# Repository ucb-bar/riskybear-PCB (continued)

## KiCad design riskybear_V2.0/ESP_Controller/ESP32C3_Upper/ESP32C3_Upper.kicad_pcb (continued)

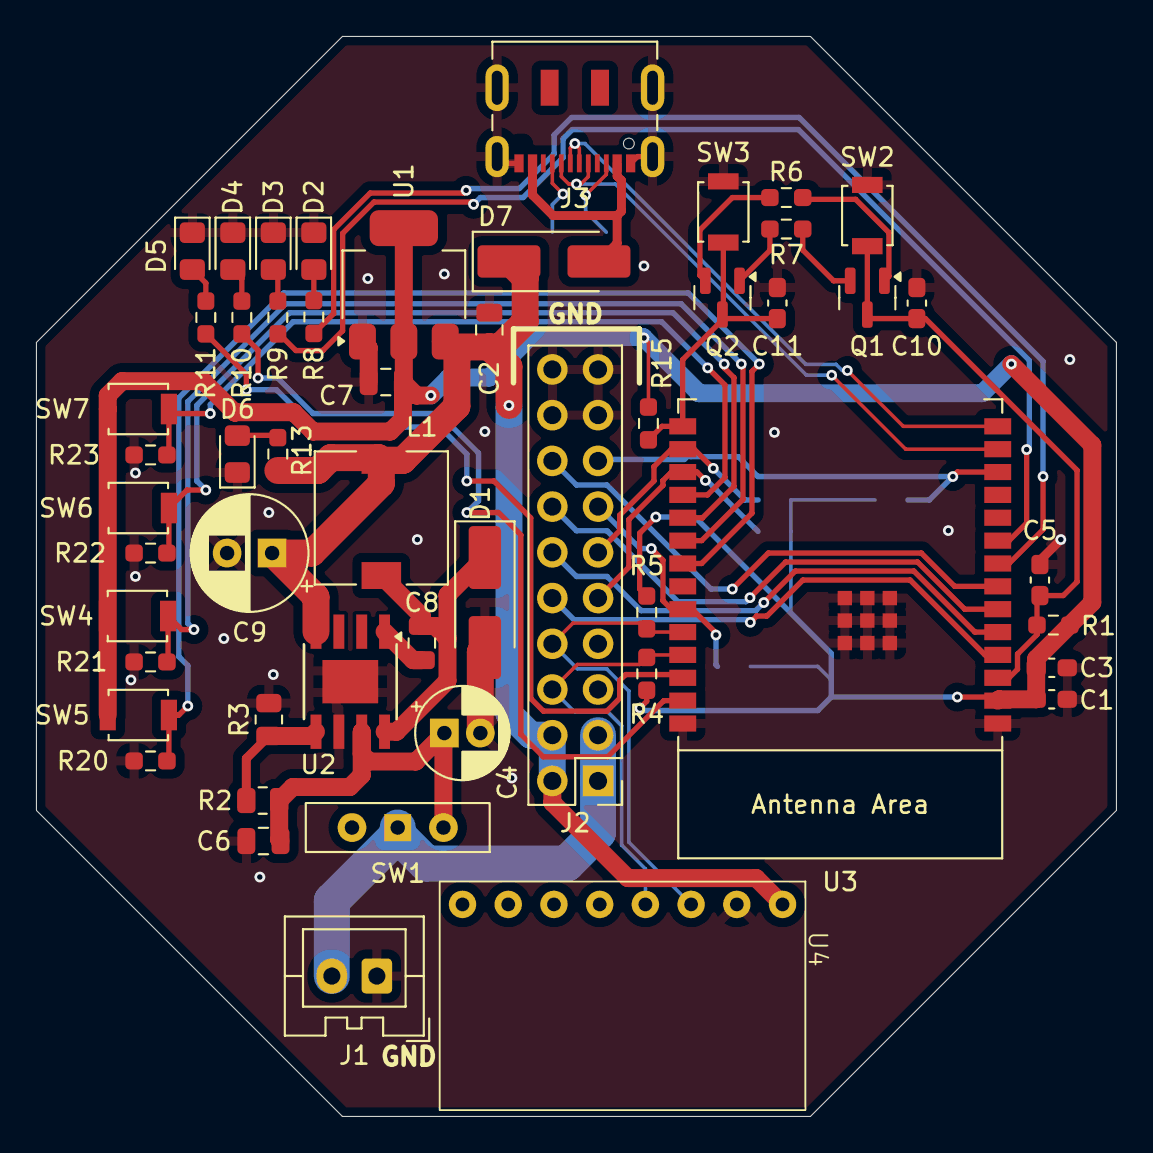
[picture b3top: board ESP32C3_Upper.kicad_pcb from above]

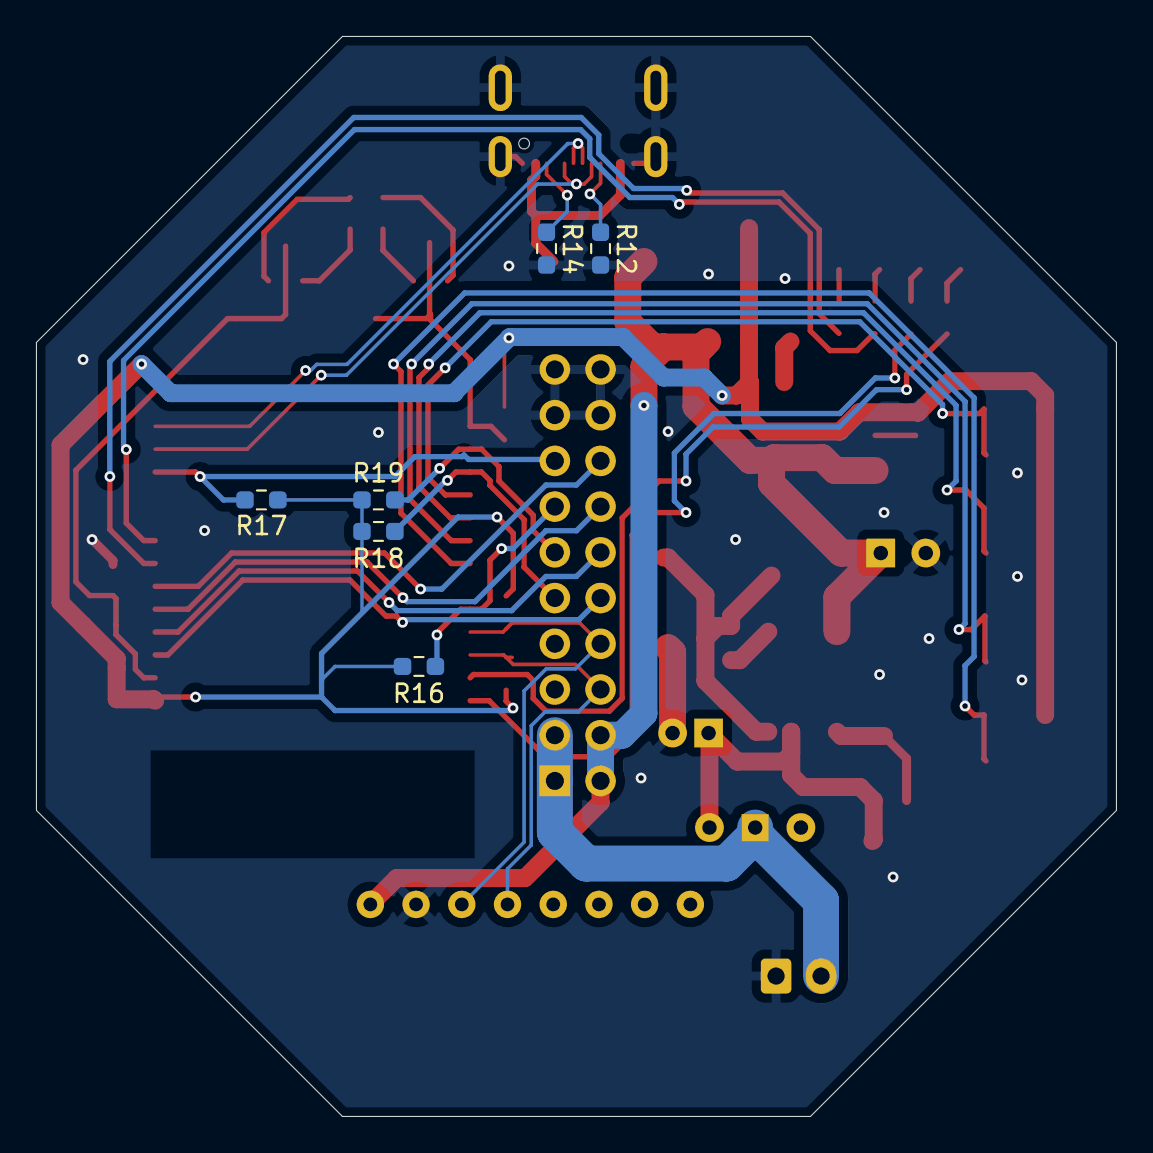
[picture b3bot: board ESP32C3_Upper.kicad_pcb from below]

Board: 2 copper layers, 60.0 x 60.0 mm, 58 parts (6 on the bottom side), 42 nets.

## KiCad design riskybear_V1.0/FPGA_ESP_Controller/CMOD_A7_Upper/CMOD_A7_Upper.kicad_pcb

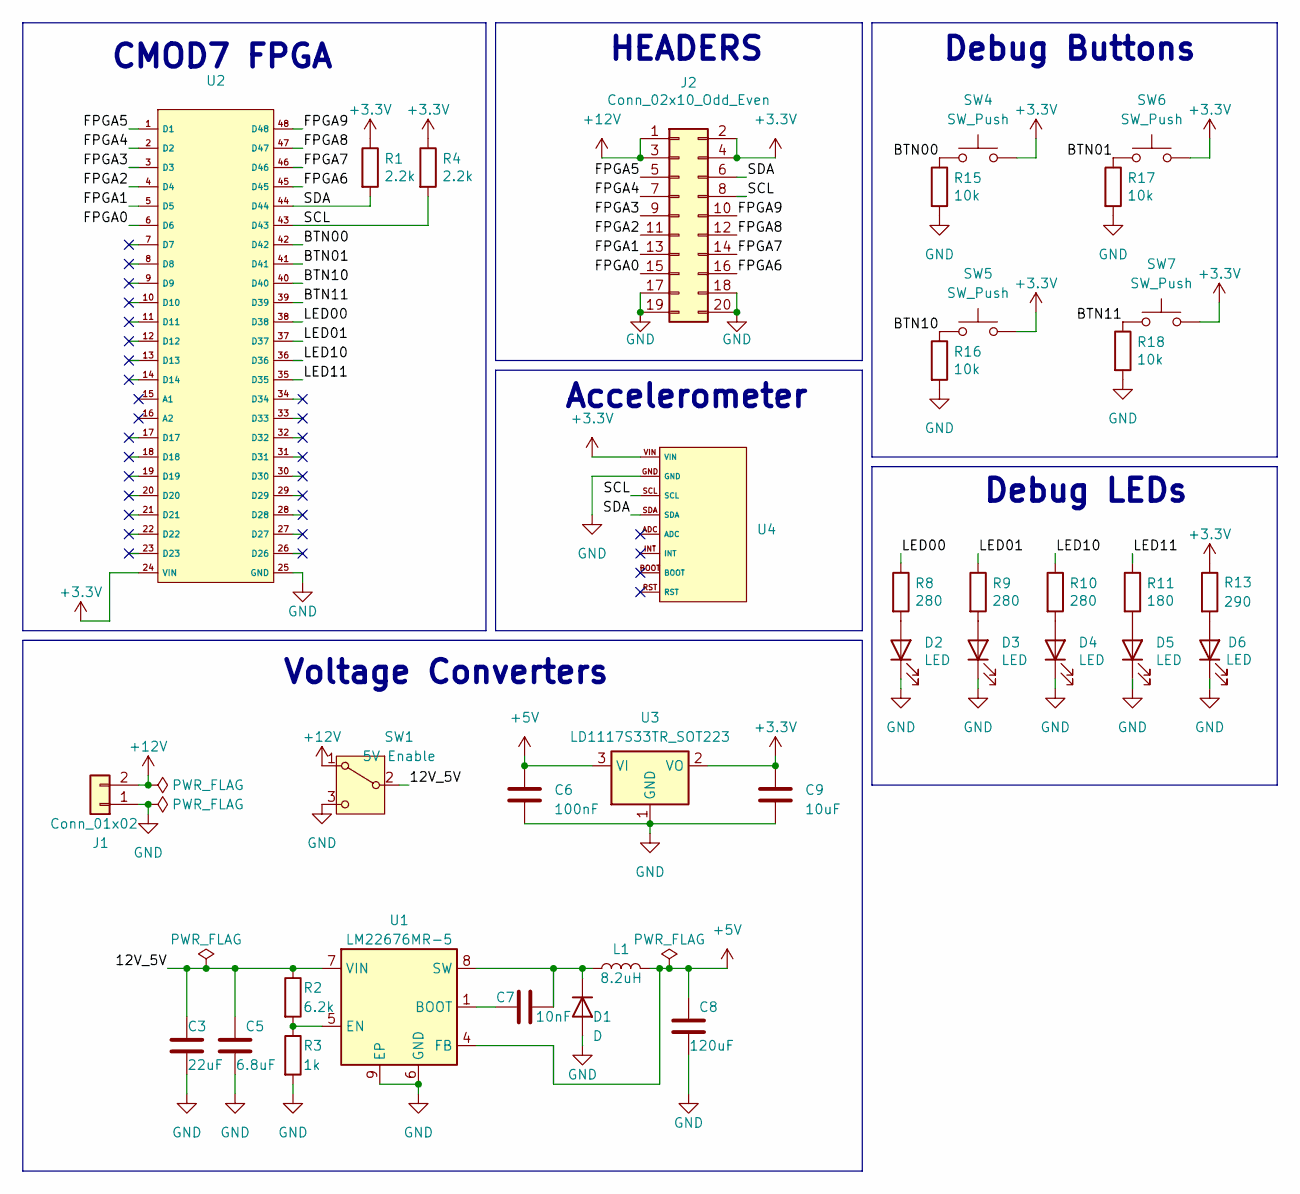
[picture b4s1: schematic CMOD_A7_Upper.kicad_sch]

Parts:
C3: 22uF; CP_Radial_D5.0mm_P2.00mm
C5: 6.8uF; C_0805_2012Metric
C6: 100nF; C_0805_2012Metric
C7: 10nF; C_0805_2012Metric
C8: 120uF; CP_Radial_D6.3mm_P2.50mm
C9: 10uF; C_0805_2012Metric
D1: D; D_SMA_Handsoldering
D2, D3, D4, D5, D6: LED; LED_0805_2012Metric_Pad1.15x1.40mm_HandSolder
J1: Conn_01x02; JST_XA_B02B-XASK-1_1x02_P2.50mm_Vertical
J2: Conn_02x10_Odd_Even; PinHeader_2x10_P2.54mm_Vertical
L1: 8.2uH; L_7.3x7.3_H3.5
R1, R4: 2.2k; R_0603_1608Metric_Pad0.98x0.95mm_HandSolder
R2: 6.2k; R_0805_2012Metric
R3: 1k; R_0805_2012Metric
R8, R9, R10: 280; R_0603_1608Metric_Pad0.98x0.95mm_HandSolder
R11: 180; R_0603_1608Metric_Pad0.98x0.95mm_HandSolder
R13: 290; R_0603_1608Metric_Pad0.98x0.95mm_HandSolder
R15, R16, R17, R18: 10k; R_0603_1608Metric_Pad0.98x0.95mm_HandSolder
SW1: 5V Enable; SW_Slide-03_Wuerth-WS-SLTV_10x2.5x6.4_P2.54mm
SW4, SW5, SW6, SW7: SW_Push; SW_SPST_B3U-1000P
U1: LM22676MR-5; TI_SO-PowerPAD-8
U2: CMODA7
U3: LD1117S33TR_SOT223; SOT-223-3_TabPin2
U4: BNO055

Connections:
+3.3V: C9.1, J2.2, J2.4, R1.1, R4.1, R13.1, SW4.2, SW5.2, SW6.2, SW7.2, U2.24 (VIN), U3.2 (VO), U4.VIN
+5V: C6.1, C8.1, L1.2, U1.4 (FB), U3.3 (VI)
+12V: J1.2, J2.1, J2.3, SW1.1 (A)
/12V_5V: C3.1, C5.1, R2.1, SW1.2 (B), U1.7 (VIN)
/BTN00: R15.1, SW4.1, U2.42 (D42)
/BTN01: R17.1, SW6.1, U2.41 (D41)
/BTN10: R16.1, SW5.1, U2.40 (D40)
/BTN11: R18.1, SW7.1, U2.39 (D39)
/FPGA0: J2.15, U2.6 (D6)
/FPGA1: J2.13, U2.5 (D5)
/FPGA2: J2.11, U2.4 (D4)
/FPGA3: J2.9, U2.3 (D3)
/FPGA4: J2.7, U2.2 (D2)
/FPGA5: J2.5, U2.1 (D1)
/FPGA6: J2.16, U2.45 (D45)
/FPGA7: J2.14, U2.46 (D46)
/FPGA8: J2.12, U2.47 (D47)
/FPGA9: J2.10, U2.48 (D48)
/LED00: R8.1, U2.38 (D38)
/LED01: R9.1, U2.37 (D37)
/LED10: R10.1, U2.36 (D36)
/LED11: R11.1, U2.35 (D35)
/SCL: J2.8, R4.2, U2.43 (D43), U4.SCL
/SDA: J2.6, R1.2, U2.44 (D44), U4.SDA
GND: C3.2, C5.2, C6.2, C8.2, C9.2, D1.2 (A), D2.1 (K), D3.1 (K), D4.1 (K), D5.1 (K), D6.1 (K), J1.1, J2.17, J2.18, J2.19, J2.20, R3.2, R15.2, R16.2, R17.2, R18.2, SW1.3 (C), U1.6 (GND), U1.9 (EP), U2.25 (GND), U3.1 (GND), U4.GND
unnamed: C7.2, D1.1 (K), L1.1, U1.8 (SW)
unnamed: D2.2 (A), R8.2
unnamed: D3.2 (A), R9.2
unnamed: D4.2 (A), R10.2
unnamed: D5.2 (A), R11.2
unnamed: D6.2 (A), R13.2
unnamed: C7.1, U1.1 (BOOT)
unnamed: R2.2, R3.1, U1.5 (EN)

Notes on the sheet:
Accelerometer
CMOD7 FPGA
Voltage Converters
Debug Buttons
HEADERS
Debug LEDs

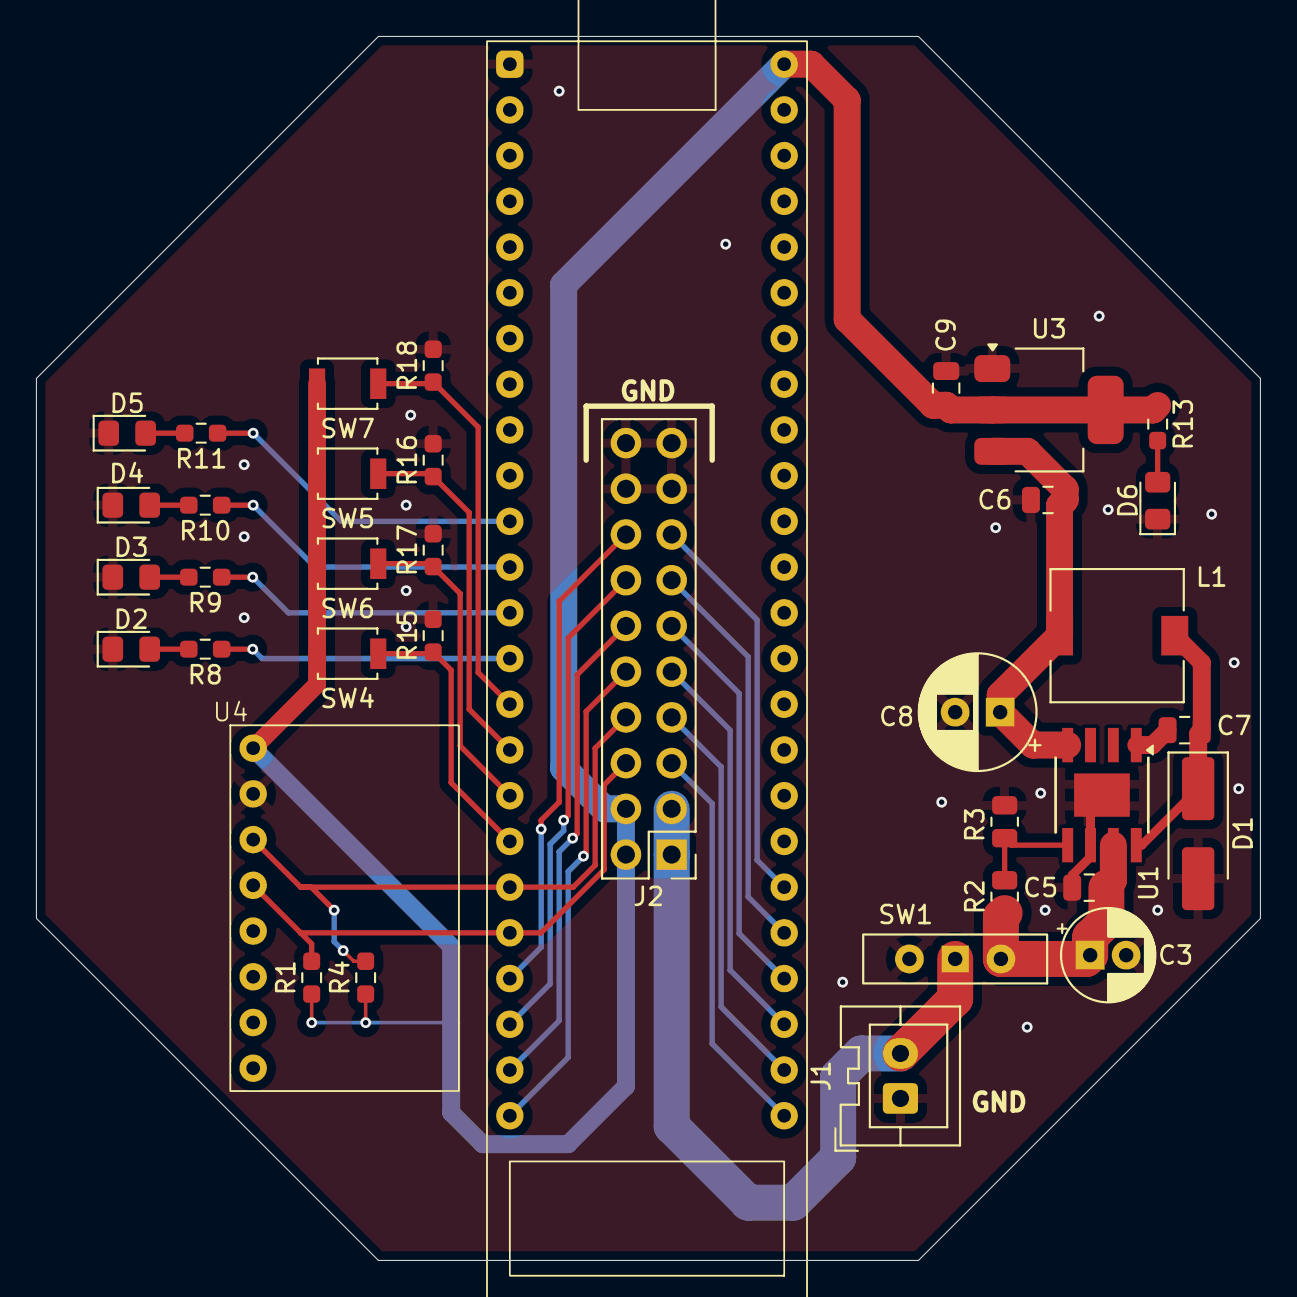
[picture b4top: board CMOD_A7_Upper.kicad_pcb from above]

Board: 2 copper layers, 68.0 x 68.0 mm, 37 parts (0 on the bottom side), 33 nets.

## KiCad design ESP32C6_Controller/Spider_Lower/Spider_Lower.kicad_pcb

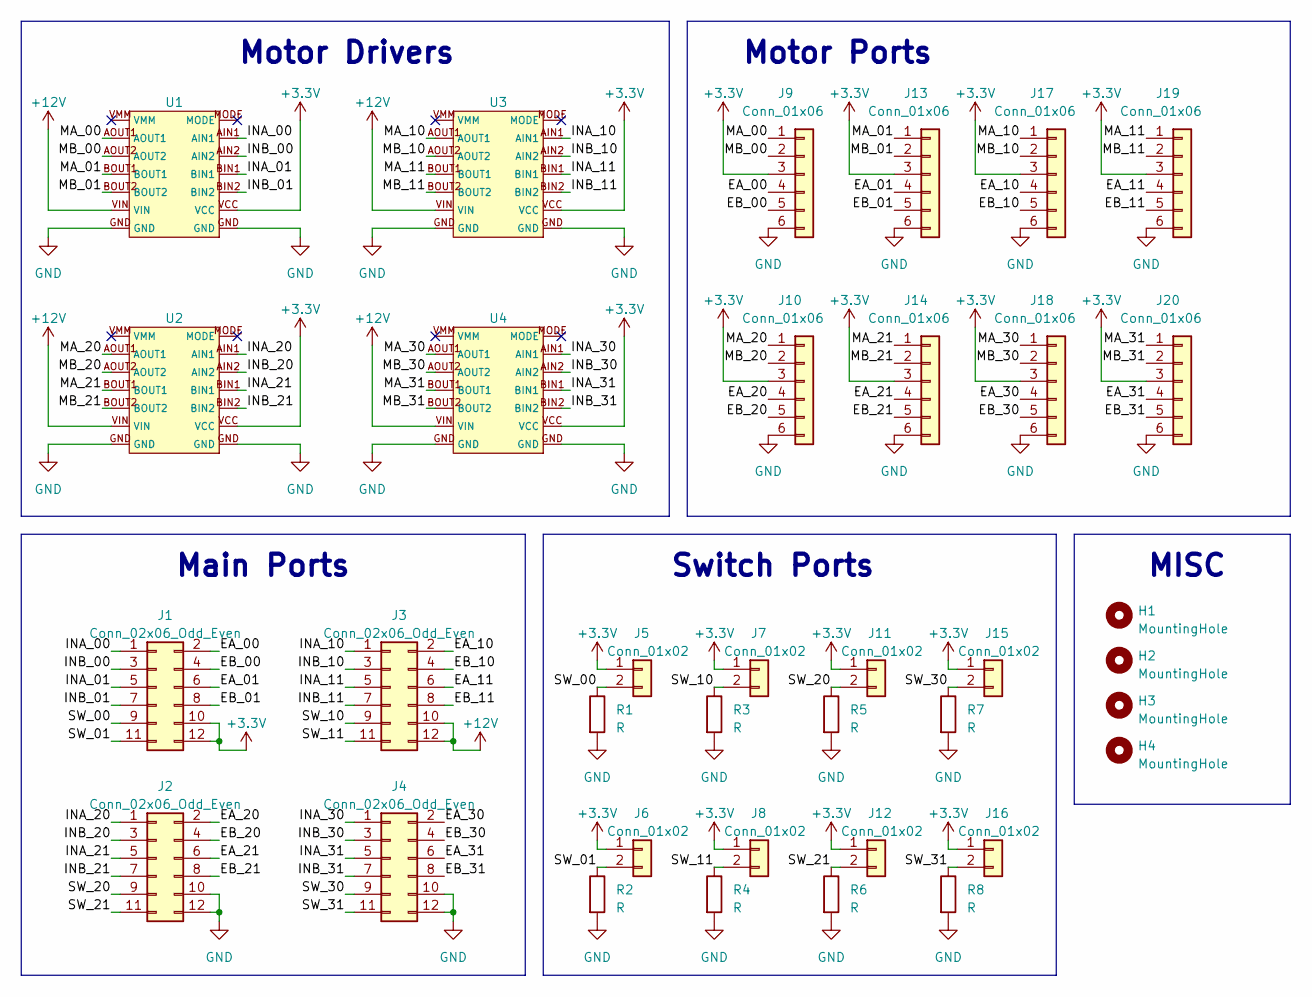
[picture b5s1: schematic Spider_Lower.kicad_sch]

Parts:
H1, H2, H3, H4: MountingHole; MountingHole_3.2mm_M3
J1, J2, J3, J4: Conn_02x06_Odd_Even; PinHeader_2x06_P2.54mm_Vertical
J5, J6, J7, J8, J11, J12, J15, J16: Conn_01x02; PinHeader_1x02_P2.54mm_Vertical
J9, J10, J13, J14, J17, J18, J19, J20: Conn_01x06; JST_SH_BM06B-SRSS-TB_1x06-1MP_P1.00mm_Vertical
R1, R2, R4, R5, R6, R7, R8: R; R_0805_2012Metric
R3: R; C_0805_2012Metric
U1, U2, U3, U4: DRV8835

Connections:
+3.3V: J1.10, J1.12, J5.1, J6.1, J7.1, J8.1, J9.3, J10.3, J11.1, J12.1, J13.3, J14.3, J15.1, J16.1, J17.3, J18.3, J19.3, J20.3, U1.VCC, U2.VCC, U3.VCC, U4.VCC
+12V: J3.10, J3.12, U1.VIN, U2.VIN, U3.VIN, U4.VIN
/EA_00: J1.2, J9.4
/EA_01: J1.6, J13.4
/EA_10: J3.2, J17.4
/EA_11: J3.6, J19.4
/EA_20: J2.2, J10.4
/EA_21: J2.6, J14.4
/EA_30: J4.2, J18.4
/EA_31: J4.6, J20.4
/EB_00: J1.4, J9.5
/EB_01: J1.8, J13.5
/EB_10: J3.4, J17.5
/EB_11: J3.8, J19.5
/EB_20: J2.4, J10.5
/EB_21: J2.8, J14.5
/EB_30: J4.4, J18.5
/EB_31: J4.8, J20.5
/INA_00: J1.1, U1.AIN1
/INA_01: J1.5, U1.BIN1
/INA_10: J3.1, U3.AIN1
/INA_11: J3.5, U3.BIN1
/INA_20: J2.1, U2.AIN1
/INA_21: J2.5, U2.BIN1
/INA_30: J4.1, U4.AIN1
/INA_31: J4.5, U4.BIN1
/INB_00: J1.3, U1.AIN2
/INB_01: J1.7, U1.BIN2
/INB_10: J3.3, U3.AIN2
/INB_11: J3.7, U3.BIN2
/INB_20: J2.3, U2.AIN2
/INB_21: J2.7, U2.BIN2
/INB_30: J4.3, U4.AIN2
/INB_31: J4.7, U4.BIN2
/MA_00: J9.1, U1.AOUT1
/MA_01: J13.1, U1.BOUT1
/MA_10: J17.1, U3.AOUT1
/MA_11: J19.1, U3.BOUT1
/MA_20: J10.1, U2.AOUT1
/MA_21: J14.1, U2.BOUT1
/MA_30: J18.1, U4.AOUT1
/MA_31: J20.1, U4.BOUT1
/MB_00: J9.2, U1.AOUT2
/MB_01: J13.2, U1.BOUT2
/MB_10: J17.2, U3.AOUT2
/MB_11: J19.2, U3.BOUT2
/MB_20: J10.2, U2.AOUT2
/MB_21: J14.2, U2.BOUT2
/MB_30: J18.2, U4.AOUT2
/MB_31: J20.2, U4.BOUT2
/SW_00: J1.9, J5.2, R1.1
/SW_01: J1.11, J6.2, R2.1
/SW_10: J3.9, J7.2, R3.1
/SW_11: J3.11, J8.2, R4.1
/SW_20: J2.9, J11.2, R5.1
/SW_21: J2.11, J12.2, R6.1
/SW_30: J4.9, J15.2, R7.1
/SW_31: J4.11, J16.2, R8.1
GND: J2.10, J2.12, J4.10, J4.12, J9.6, J10.6, J13.6, J14.6, J17.6, J18.6, J19.6, J20.6, R1.2, R2.2, R3.2, R4.2, R5.2, R6.2, R7.2, R8.2, U1.GND, U2.GND, U3.GND, U4.GND

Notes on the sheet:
Main Ports
Motor Ports
Motor Drivers
Switch Ports
MISC

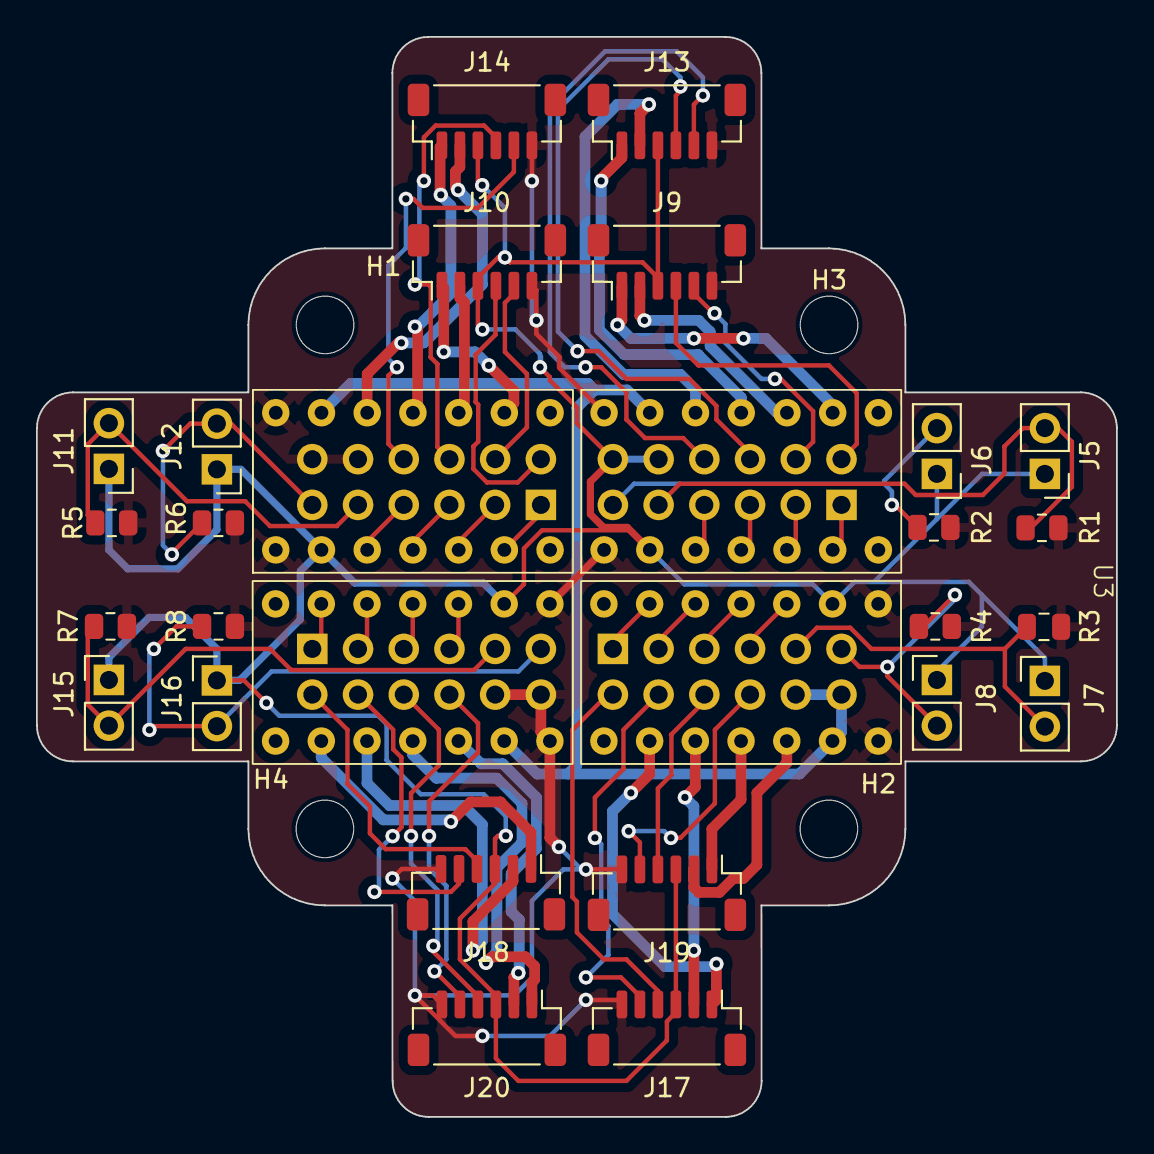
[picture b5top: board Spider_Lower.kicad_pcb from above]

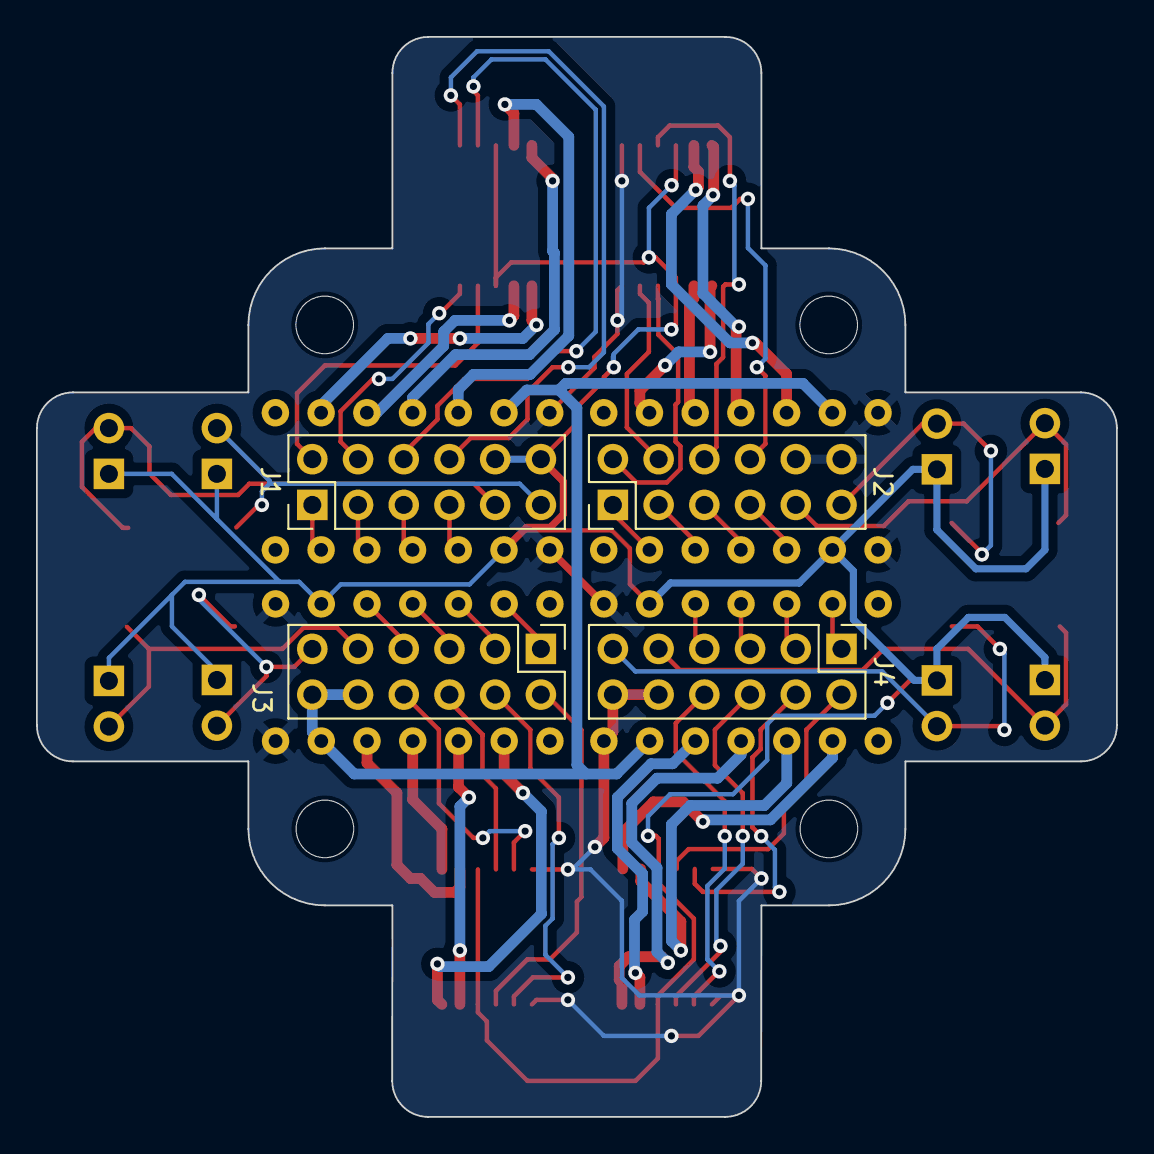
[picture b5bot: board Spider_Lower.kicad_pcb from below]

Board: 2 copper layers, 60.0 x 60.0 mm, 36 parts (4 on the bottom side), 59 nets.

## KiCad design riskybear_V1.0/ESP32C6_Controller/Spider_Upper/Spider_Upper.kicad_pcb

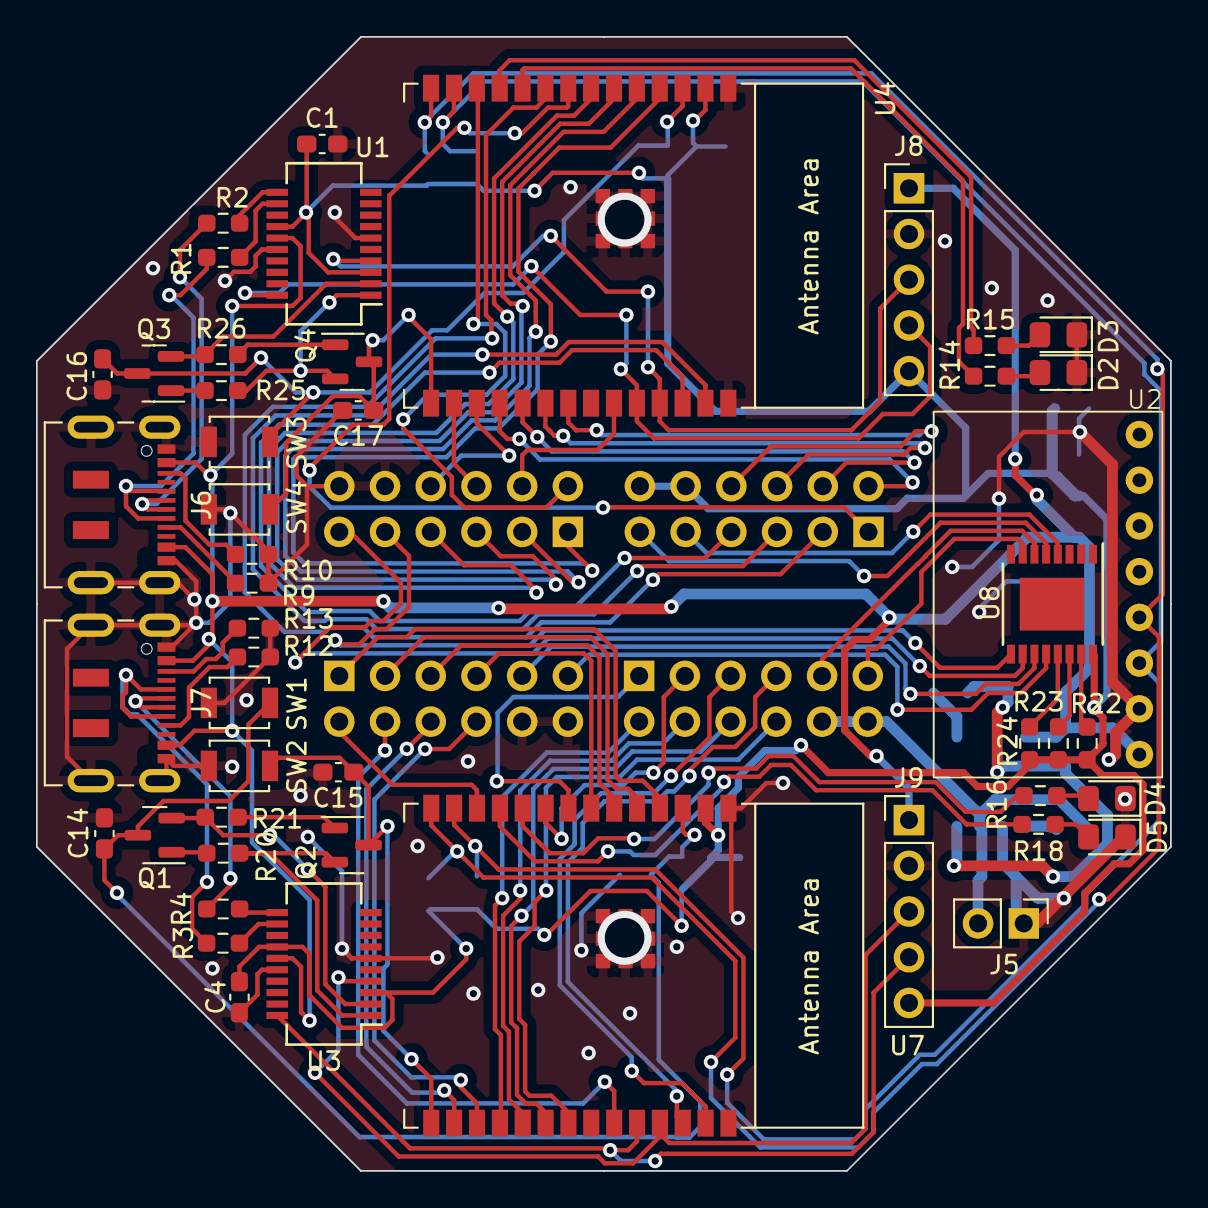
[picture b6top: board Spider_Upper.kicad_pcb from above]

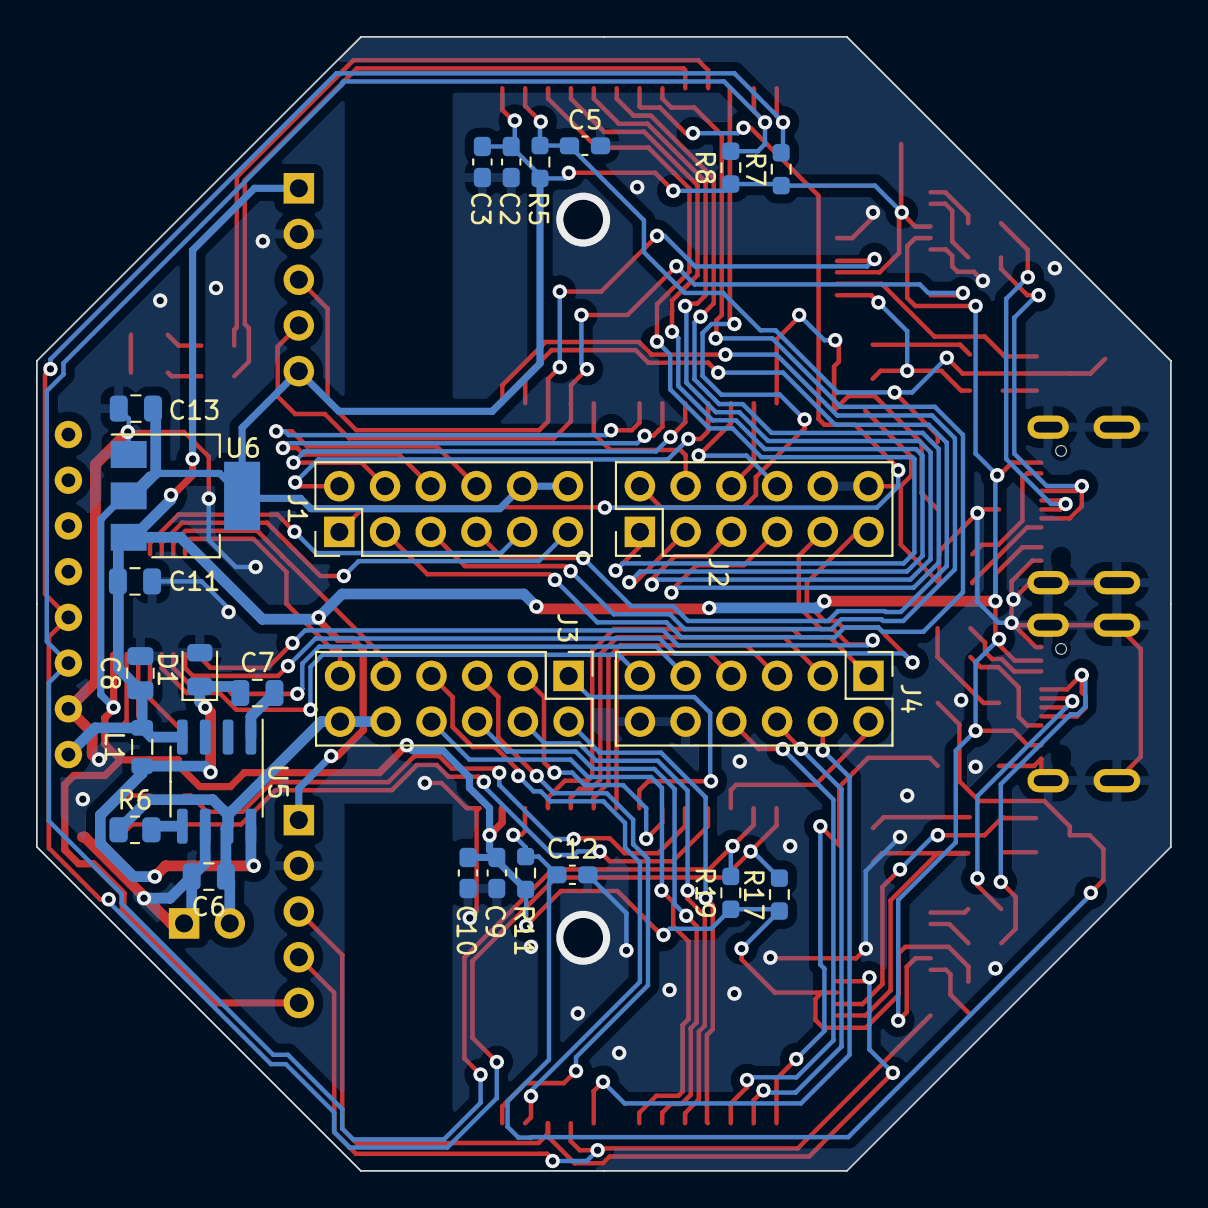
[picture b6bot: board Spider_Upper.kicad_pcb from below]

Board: 2 copper layers, 63.0 x 63.0 mm, 74 parts (26 on the bottom side), 88 nets.

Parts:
C1, C3, C4, C5, C10, C12, C14, C15, C16, C17: 0.1u; C_0603_1608Metric_Pad1.08x0.95mm_HandSolder
C2, C9: 10u; C_0603_1608Metric_Pad1.08x0.95mm_HandSolder
C6: 100uF; C_0805_2012Metric
C7: 10nF; C_0805_2012Metric
C8: 68uF; C_0805_2012Metric
C11: 100nF; C_0805_2012Metric
C13: 10uF; C_0805_2012Metric
D1: D; D_0805_2012Metric
D2, D3, D4, D5: LED; LED_0805_2012Metric_Pad1.15x1.40mm_HandSolder
J1, J2, J3, J4: Conn_02x06_Odd_Even; PinHeader_2x06_P2.54mm_Vertical
J5: Conn_01x02; PinHeader_1x02_P2.54mm_Vertical
J6, J7: USB_C_Receptacle_USB2.0; USB_C_Receptacle_JAE_DX07S016JA1R1500
J8, J9: Conn_01x05; PinHeader_1x05_P2.54mm_Vertical
L1: 47uH; L_0805_2012Metric
Q1, Q2, Q3, Q4: DNBT8105-7; SOT-23
R1, R2, R3, R4: 27; R_0603_1608Metric_Pad0.98x0.95mm_HandSolder
R5, R11, R20, R21, R25, R26: 10k; R_0603_1608Metric_Pad0.98x0.95mm_HandSolder
R6: 5k; R_0805_2012Metric
R7, R8, R17, R19, R22, R23, R24: 2.2k; R_0603_1608Metric_Pad0.98x0.95mm_HandSolder
R9, R10, R12, R13: 5.1k; R_0603_1608Metric_Pad0.98x0.95mm_HandSolder
R14, R15, R16: 280; R_0603_1608Metric_Pad0.98x0.95mm_HandSolder
R18: 180; R_0603_1608Metric_Pad0.98x0.95mm_HandSolder
SW1, SW2, SW3, SW4: SW_SPST; SW_SPST_B3U-1000P
U1, U3: FT231XS; SSOP-20_3.9x8.7mm_P0.635mm
U2: BNO055
U4, U7: ESP32-C6-WROOM-1
U5: LM2675M-5; SOIC-8_3.9x4.9mm_P1.27mm
U6: LD1117S33TR_SOT223; SOT-223-3_TabPin2
U8: TSSOP-16-1EP_4.4x5mm_P0.65mm

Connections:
+3.3V: C1.1, C2.1, C3.1, C4.1, C9.1, C10.1, C13.1, J1.10, J1.12, J8.5, J9.5, R5.1, R7.1, R8.1, R11.1, R17.1, R19.1, R22.1, R23.1, R24.1, U1.3 (VCCIO), U1.14 (~RESET), U3.3 (VCCIO), U3.14 (~RESET), U4.2 (3V3), U6.2 (VO), U7.2 (3V3), U8.16 (VCC)
+5V: C8.1, C11.1, J6.A4 (VBUS), J6.A9 (VBUS), J6.B4 (VBUS), J6.B9 (VBUS), J7.A4 (VBUS), J7.A9 (VBUS), J7.B4 (VBUS), J7.B9 (VBUS), J8.1, J9.1, L1.2, U1.15 (VCC), U2.VIN, U3.15 (VCC), U5.4 (FB), U6.3 (VI)
+12V: C6.1, J3.10, J3.12, J5.2, R6.1, U5.7 (VIN)
/BOOT0: C17.1, Q4.3 (C), SW4.2 (B), U4.15 (GPIO9)
/BOOT1: C15.1, Q2.3 (C), SW2.2 (B), U7.15 (GPIO9)
/DTR0: Q4.2 (E), R25.1, U1.1 (~DTR)
/DTR1: Q2.2 (E), R20.1, U3.1 (~DTR)
/EA_00: J1.2, U4.18 (GPIO20)
/EA_01: J1.6, U4.20 (GPIO22)
/EA_10: J3.2, U7.18 (GPIO20)
/EA_11: J3.6, U7.20 (GPIO22)
/EA_20: J2.2, U4.12 (GPIO11)
/EA_21: J2.6, U4.16 (GPIO18)
/EA_30: J4.2, U7.12 (GPIO11)
/EA_31: J4.6, U7.16 (GPIO18)
/EB_00: J1.4, U4.19 (GPIO21)
/EB_01: J1.8, U4.21 (GPIO23)
/EB_10: J3.4, U7.19 (GPIO21)
/EB_11: J3.8, U7.21 (GPIO23)
/EB_20: J2.4, U4.23 (GPIO15)
/EB_21: J2.8, U4.17 (GPIO19)
/EB_30: J4.4, U7.23 (GPIO15)
/EB_31: J4.8, U7.17 (GPIO19)
/EN0: C5.1, C16.1, Q3.3 (C), R5.2, SW3.2 (B), U4.3 (EN/CHIP_PU)
/EN1: C12.1, C14.1, Q1.3 (C), R11.2, SW1.2 (B), U7.3 (EN/CHIP_PU)
/INA_00: J1.1, U4.8 (GPIO0/ADC1_CH0/XTAL_32K_P)
/INA_01: J1.5, U4.27 (GPIO2/ADC1_CH2)
/INA_10: J3.1, U7.8 (GPIO0/ADC1_CH0/XTAL_32K_P)
/INA_11: J3.5, U7.27 (GPIO2/ADC1_CH2)
/INA_20: J2.1, U4.4 (MTMS/GPIO4/ADC1_CH4)
/INA_21: J2.5, U4.6 (MTCK/GPIO6/ADC1_CH6)
/INA_30: J4.1, U7.4 (MTMS/GPIO4/ADC1_CH4)
/INA_31: J4.5, U7.6 (MTCK/GPIO6/ADC1_CH6)
/INB_00: J1.3, U4.9 (GPIO1/ADC1_CH1/XTAL_32K_N)
/INB_01: J1.7, U4.26 (GPIO3/ADC1_CH3)
/INB_10: J3.3, U7.9 (GPIO1/ADC1_CH1/XTAL_32K_N)
/INB_11: J3.7, U7.26 (GPIO3/ADC1_CH3)
/INB_20: J2.3, U4.5 (MTDI/GPIO5/ADC1_CH5)
/INB_21: J2.7, U4.7 (MTDO/GPIO7)
/INB_30: J4.3, U7.5 (MTDI/GPIO5/ADC1_CH5)
/INB_31: J4.7, U7.7 (MTDO/GPIO7)
/LED00: R14.1, U4.10 (GPIO8)
/LED01: R15.1, U4.11 (GPIO10)
/LED10: R16.1, U7.10 (GPIO8)
/LED11: R18.1, U7.11 (GPIO10)
/RTS0: Q3.2 (E), R26.1, U1.2 (~RTS)
/RTS1: Q1.2 (E), R21.1, U3.2 (~RTS)
/RX0: J8.4, U1.20 (TXD), U4.24 (U0RXD/GPIO17)
/RX1: J9.4, U3.20 (TXD), U7.24 (U0RXD/GPIO17)
/SCL: R8.2, R19.2, U2.SCL, U4.13 (GPIO12/USB_D-), U7.13 (GPIO12/USB_D-)
/SDA: R7.2, R17.2, U2.SDA, U4.14 (GPIO13/USB_D+), U7.14 (GPIO13/USB_D+)
/SW_00: J1.9, U8.4 (P0)
/SW_01: J1.11, U8.5 (P1)
/SW_10: J3.9, U8.6 (P2)
/SW_11: J3.11, U8.7 (P3)
/SW_20: J2.9, U8.9 (P4)
/SW_21: J2.11, U8.10 (P5)
/SW_30: J4.9, U8.11 (P6)
/SW_31: J4.11, U8.12 (P7)
/TX0: J8.3, U1.4 (RXD), U4.25 (U0TXD/GPIO16)
/TX1: J9.3, U3.4 (RXD), U7.25 (U0TXD/GPIO16)
/USB_DM0: J6.A7 (D-), J6.B7 (D-), R1.1
/USB_DM1: J7.A7 (D-), J7.B7 (D-), R3.1
/USB_DP0: J6.A6 (D+), J6.B6 (D+), R2.1
/USB_DP1: J7.A6 (D+), J7.B6 (D+), R4.1
GND: C1.2, C2.2, C3.2, C4.2, C5.2, C6.2, C8.2, C9.2, C10.2, C11.2, C12.2, C13.2, C14.2, C15.2, C16.2, C17.2, D1.2 (A), D2.1 (K), D3.1 (K), D4.1 (K), D5.1 (K), J2.10, J2.12, J4.10, J4.12, J5.1, J6.A1 (GND), J6.A12 (GND), J6.B1 (GND), J6.B12 (GND), J6.S1 (SHIELD), J7.A1 (GND), J7.A12 (GND), J7.B1 (GND), J7.B12 (GND), J7.S1 (SHIELD), J8.2, J9.2, R9.2, R10.2, R12.2, R13.2, SW1.1 (A), SW2.1 (A), SW3.1 (A), SW4.1 (A), U1.6 (GND), U1.16 (GND), U2.GND, U3.6 (GND), U3.16 (GND), U4.1 (GND), U4.28 (GND), U4.29 (GND), U5.6 (GND), U6.1 (GND), U7.1 (GND), U7.28 (GND), U7.29 (GND), U8.8 (GND)
unnamed: C7.1, D1.1 (K), L1.1, U5.8 (VSW)
unnamed: D2.2 (A), R14.2
unnamed: D3.2 (A), R15.2
unnamed: D4.2 (A), R16.2
unnamed: D5.2 (A), R18.2
unnamed: J6.A5 (CC1), R10.1
unnamed: J6.B5 (CC2), R9.1
unnamed: J7.A5 (CC1), R13.1
unnamed: J7.B5 (CC2), R12.1
unnamed: Q1.1 (B), R20.2
unnamed: Q2.1 (B), R21.2
unnamed: Q3.1 (B), R25.2
unnamed: Q4.1 (B), R26.2
unnamed: R1.2, U1.12 (USBDM)
unnamed: R2.2, U1.11 (USBDP)
unnamed: R3.2, U3.12 (USBDM)
unnamed: R4.2, U3.11 (USBDP)
unnamed: C7.2, U5.1 (CB)
unnamed: R6.2, U5.5 (ON/~OFF)
unnamed: R24.2, U8.13 (NINT)
unnamed: R23.2, U8.14 (SCL)
unnamed: R22.2, U8.15 (SDA)

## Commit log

2024-02-16 moved files over
2024-04-19 new PCBs
2024-04-19 added ignore
2024-07-01 updated pcbs
